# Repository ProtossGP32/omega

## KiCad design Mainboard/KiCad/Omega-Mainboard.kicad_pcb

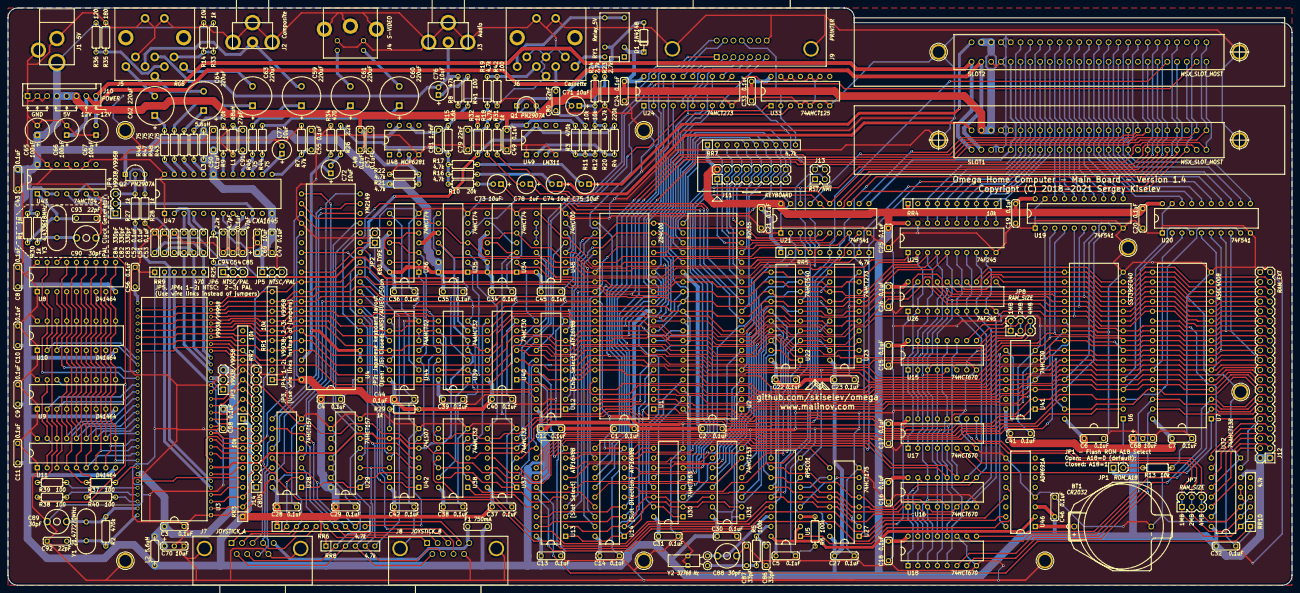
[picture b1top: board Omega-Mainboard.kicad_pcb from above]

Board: 2 copper layers, 333.4 x 149.9 mm, 248 parts (0 on the bottom side), 357 nets.

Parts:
BT1: CR2032; Battery_Holder_CR2032_Universal
C1, C2, C3, C4, C5, C6, C7, C8, C9, C10, C11, C12, C13, C14, C15, C16, C17, C18, C19, C20, C21, C22, C23, C24, C25, C26, C27, C28, C29, C30, C31, C32, C33, C34, C35, C36, C37, C38, C39, C40, C41, C42, C43, C44, C45, C46, C47, C48, C49, C50, C51, C52, C53, C54, C55, C56, C57, C58: 0.1uF; Cap_Cer_508
C59, C60, C61, C62, C63, C64: 220uF; Cap_Elec_Radial_10mm
C65, C66, C67: 100uF; Cap_Elec_Radial_6.3mm
C68, C69, C70: 10uF; Cap_Pol_508_3
C71, C72, C73, C74, C75, C76, C77: 10uF; Cap_Elec_Radial_5mm
C78: 1uF; Cap_Elec_Radial_5mm
C79, C80: 22nF; Cap_Cer_508
C81: 1.5nF; Cap_Cer_508
C82, C83, C84: 330pF; Cap_Cer_508
C85: 47pF; Cap_Cer_508
C86, C87: 33pF; Cap_Cer_508
C88, C89, C90: 30pF; C_Trim_Murata
C91: 27pF; Cap_Cer_508
C92, C93: 22pF; Cap_Cer_508
C94: 4.7pF; Cap_Cer_508
D1: 1N4148; Diode_762
F1: 750mA; Cap_Cer_508
HOLE1, HOLE2, HOLE3, HOLE4, HOLE5, HOLE6, HOLE7, HOLE8, HOLE9, HOLE10, HOLE11: HOLE; Hole_3mm
J1: 5V; Conn_Power_Jack_Circular_Pads
J2: Composite; Conn_RCA_Composite
J3: Audio; Conn_RCA_Audio
J4: S-VIDEO; Conn_Mini_DIN_4pin
J5: RGB; Conn_DIN_8pin
J6: Cassette; Conn_DIN_8pin
J7: JOYSTICK_A; Conn_Dsub_DE9M
J8: JOYSTICK_B; Conn_Dsub_DE9M
J9: PRINTER; Conn_Micro_Ribbon_14F
J10: POWER; Conn_Friction_Lock_8P_2.54mm
J11: KEYBOARD; Conn_Pin_Header_8x2_2.54mm
J12: RAM_EXT; Conn_Pin_Header_20x2_2.54mm
J13: ~RST~/~NMI; Conn_Pin_Header_2x2_2.54mm
J14: CBUS; Conn_Pin_Header_13x1_2.54mm
JP1: ROM_A18; Conn_Pin_Header_2x1_2.54mm
JP2: KBD_TYPE; Conn_Pin_Header_2x1_2.54mm
JP3, JP4: V9938/V9958; Conn_Pin_Header_3x1_2.54mm
JP5, JP6: NTSC/PAL; Conn_Pin_Header_3x1_2.54mm
JP7, JP8: RAM_SIZE; Conn_Pin_Header_2x3_2.54mm
L1: 68uH; Res_762
L2, L3: 5.6uH; Res_762
Q1, Q2: PN2907A; Transistor_TO92_EBC_254
R1: 1M; Res_762
R2, R3: 470k; Res_762
R4: 220k; Res_762
R5, R6: 100k; Res_762
R7, R8: 47k; Res_762
R9, R10: 20k; Res_762
R11, R12, R13, R14: 10k; Res_762
R15: 5.6k; Res_762
R16, R17, R18, R19, R20, R21, R22: 4.7k; Res_762
R23, R24: 2.7k; Res_762
R25, R26: 2.2k; Res_762
R27, R28, R29, R30, R31, R32, R33: 1k; Res_762
R34: 470; Res_762
R35: 180; Res_762
R36: 120; Res_762
R37, R38, R39, R40, R41, R42: 100; Res_762
R43, R44, R45, R46, R47, R48: 75; Res_762
RR1, RR2, RR3, RR4: 10k; Conn_SIL10
RR5, RR6, RR7: 4.7k; Conn_SIL10
RR8, RR10: 4.7k; Conn_SIL6
RR9: 470; Conn_SIL6
RY1: Relay_5V; Relay_SPDT
SLOT1, SLOT2: MSX_SLOT_HOST; Conn_Edge_50P
U1: Z84C00; IC_DIP40_600
U2: 82C55; IC_DIP40_600
U3: V9938/V9958; IC_SDIP64_600
U4: YM2149; IC_DIP40_600
U5: RP5C01; IC_DIP18_300
U6: SST39SF040; IC_DIP32_600
U7: AS6C4008; IC_DIP32_600
U8, U9, U10, U11: D41464; IC_DIP18_300
U12, U13, U14: ATF16V8B; IC_DIP20_300
U15, U16, U17, U18: 74HCT670; IC_DIP16_300
U19, U20, U21: 74F541; IC_DIP20_300
U22: 74HCT540; IC_DIP20_300
U23, U24: 74HCT273; IC_DIP20_300
U25, U26: 74F245; IC_DIP20_300
U27: 74HCT175; IC_DIP16_300
U28, U29: 74HCT157; IC_DIP16_300
U30, U31: 74HCT153; IC_DIP16_300
U32: 74AHCT138; IC_DIP16_300
U33: 74AHCT125; IC_DIP14_300
U34, U35, U36: 74HCT74; IC_DIP14_300
U37, U38, U39: 74AHCT32; IC_DIP14_300
U40, U41: 74HCT30; IC_DIP14_300
U42: 74LS07; IC_DIP14_300
U43: 74HCT04; IC_DIP14_300
U44: 74AHCT02; IC_DIP14_300
U45: 74HCT00; IC_DIP14_300
U46: ADM691A; IC_DIP16_300
U47: CXA1645; IC_DIP24_400
U48: MCP6281; IC_DIP8_300
U49: LM311; IC_DIP8_300
Y1: 21.477270MHz; Crystal_HC-49U_Vert
Y2: 32768 Hz; Crystal_32K_Horiz
Y3: 4.433618MHz; Crystal_HC-49U_Vert

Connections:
/A0: J12.31, U1.30, U2.9, U3.29, U6.12, U7.12, U12.9, U15.5, U15.14, U16.5, U16.14, U17.14, U18.14, U19.7, U40.12, U44.9
/A1: J12.29, U1.31, U2.8, U3.28, U6.11, U7.11, U15.4, U15.13, U16.4, U16.13, U17.13, U18.13, U19.6, U40.11, U44.11
/A2: J12.27, U1.32, U6.10, U7.10, U12.8, U19.5, U40.6
/A3: J12.25, U1.33, U6.9, U7.9, U12.7, U19.4, U40.5
/A4: J12.23, U1.34, U6.8, U7.8, U12.6, U19.3, U40.4
/A5: J12.21, U1.35, U6.7, U7.7, U12.5, U19.2, U40.3
/A6: J12.19, U1.36, U6.6, U7.6, U12.4, U20.5, U40.2
/A7: J12.17, U1.37, U6.5, U7.5, U12.3, U20.4, U40.1
/A8: J12.20, U1.38, U6.27, U7.27, U20.3, U41.11
/A9: J12.22, U1.39, U6.26, U7.26, U20.8, U41.5
/A10: J12.28, U1.40, U6.23, U7.23, U20.7, U41.4
/A11: J12.24, U1.1, U6.25, U7.25, U20.6, U41.6
/A12: J12.15, U1.2, U6.4, U7.4, U20.2, U41.3
/A13: J12.18, U1.3, U6.28, U7.28, U19.9, U41.12
/A14: U1.4, U6.29, U13.2, U14.2, U17.5, U18.5, U19.8, U30.14, U31.14, U41.2
/A15: U1.5, U6.3, U13.1, U14.1, U17.4, U18.4, U20.9, U30.2, U31.2, U41.1
/AUDIO: C76.2, J3.1, J5.2, R8.1
/CAS_IN: R4.2, R32.1, U4.14, U49.7
/CAS_MOT: R31.1, U2.13
/CAS_OUT: C78.1, U2.12
/CLK: U3.8, U21.9, U35.11, U39.4, U39.5, U42.5, U42.9
/D0: RR1.3, U1.14, U2.34, U3.40, U4.37, U5.11, U16.3, U16.6, U18.3, U22.18, U23.3, U24.17, U25.9, U26.9, U27.5, U35.2
/D1: RR1.4, U1.15, U2.33, U3.39, U4.36, U5.12, U16.2, U16.7, U18.2, U22.17, U23.18, U24.14, U25.8, U26.8, U27.4, U33.3
/D2: RR1.5, U1.12, U2.32, U3.38, U4.35, U5.13, U16.1, U16.9, U18.1, U22.16, U23.17, U24.4, U25.7, U26.7, U27.12
/D3: RR1.6, U1.8, U2.31, U3.37, U4.34, U5.14, U16.10, U16.15, U18.15, U22.15, U23.4, U24.7, U25.6, U26.6, U27.13
/D4: RR1.7, U1.7, U2.30, U3.36, U4.33, U15.3, U15.6, U17.3, U22.14, U23.7, U24.13, U25.5, U26.5
/D5: JP8.5, JP8.6, RR1.8, U1.9, U2.29, U3.35, U4.32, U15.2, U15.7, U17.2, U22.13, U23.14, U24.8, U25.4, U26.4
/D6: JP8.1, JP8.2, RR1.9, U1.10, U2.28, U3.34, U4.31, U15.10, U15.15, U17.15, U22.12, U23.13, U24.18, U25.3, U26.3
/D7: JP8.3, JP8.4, RR1.10, U1.13, U2.27, U3.32, U4.30, U15.1, U15.9, U17.1, U22.11, U23.8, U24.3, U25.2, U26.2
/KANA_LED: J11.14, U4.6
/KEY_CLICK: C73.1, U2.10
/Memory/MD0: J12.33, U6.13, U7.13, U26.11
/Memory/MD1: J12.35, U6.14, U7.14, U26.12
/Memory/MD2: J12.37, U6.15, U7.15, U26.13
/Memory/MD3: J12.38, U6.17, U7.17, U26.14
/Memory/MD4: J12.36, U6.18, U7.18, U26.15
/Memory/MD5: J12.34, U6.19, U7.19, U26.16
/Memory/MD6: J12.32, U6.20, U7.20, U26.17
/Memory/MD7: J12.30, U6.21, U7.21, U26.18
/Memory/RAM_A14: J12.13, U7.3, U18.6
/Memory/RAM_A15: J12.12, U7.31, U18.7
/Memory/RAM_A16: J12.11, U7.2, U18.9
/Memory/RAM_A17: J12.14, U7.30, U18.10
/Memory/RAM_A18: J12.9, U7.1, U17.6
/Memory/RAM_A19: JP7.1, JP7.2, RR10.2, U17.7, U32.1
/Memory/RAM_A20: JP7.3, JP7.4, RR10.3, U17.10, U32.2
/Memory/RAM_A21: JP7.5, JP7.6, RR10.4, U17.9, U32.3
/Memory/ROM_A18: JP1.2, R13.1, U6.1
/Memory/~PAGE_RD: U15.11, U16.11, U37.3
/Memory/~PAGE_WR: U15.12, U16.12, U17.12, U18.12, U37.11
/Memory/~RAM0_CS: U7.22, U32.15
/Memory/~RAM1_CS: J12.4, U32.14
/Memory/~RAM2_CS: J12.3, U32.13
/Memory/~RAM3_CS: J12.6, U32.12
/Memory/~RAM4_CS: J12.5, U32.11
/Memory/~RAM5_CS: J12.8, U32.10
/Memory/~RAM6_CS: J12.7, U32.9
/Memory/~RAM7_CS: J12.10, U32.7
/PPI/CAPS_LED: J11.12, U2.11
/PPI/COLUMN0: J11.1, RR7.2, U2.18
/PPI/COLUMN1: J11.3, RR7.3, U2.19
/PPI/COLUMN2: J11.5, RR7.4, U2.20
/PPI/COLUMN3: J11.7, RR7.5, U2.21
/PPI/COLUMN4: J11.9, RR7.6, U2.22
/PPI/COLUMN5: J11.11, RR7.7, U2.23
/PPI/COLUMN6: J11.13, RR7.8, U2.24
/PPI/COLUMN7: J11.15, RR7.9, U2.25
/PPI/ROW_A: J11.4, U2.14
/PPI/ROW_B: J11.6, U2.15
/PPI/ROW_C: J11.8, U2.16
/PPI/ROW_D: J11.10, U2.17
/PPI/SB_SLT_A: U13.6, U31.7
/PPI/SB_SLT_B: U13.7, U31.9
/PPI/SLT_A: U13.8, U30.7
/PPI/SLT_B: U13.9, U30.9
/PPI/~FFFF: U13.5, U38.2, U38.6
/PPI/~SLTSL3: U13.17, U38.1
/PPI/~SUB_RD: U22.1, U22.19, U38.11
/PPI/~SUB_REG_CS: U38.3, U38.10, U38.12
/PPI/~SUB_WR: U23.11, U38.8
/PRT_BUSY: J9.11, RR7.10, U33.2
/PSG/JB0: U4.13, U42.1
/PSG/JB1: U4.12, U42.13
/PSG/JB2: U4.11, U42.11
/PSG/JB3: U4.10, U42.3
/PSG/JOY_BCK: U4.20, U28.7
/PSG/JOY_FWD: U4.21, U28.4
/PSG/JOY_LFT: U4.19, U28.9
/PSG/JOY_OUT_A: J7.8, U4.9
/PSG/JOY_OUT_B: J8.8, U4.8
/PSG/JOY_RGT: U4.18, U28.12
/PSG/JOY_SEL: U4.7, U28.1, U29.1
/PSG/JOY_TRG1: U4.17, U29.4
/PSG/JOY_TRG2: U4.16, U29.7
/PSG/KBD_TYPE: JP2.1, RR8.6, U4.15
/PSG/PSG_BC1: U4.29, U44.10
/PSG/PSG_BDIR: U4.27, U44.13
/PSG/~BCK_A: J7.2, RR6.3, U28.5
/PSG/~BCK_B: J8.2, RR6.7, U28.6
/PSG/~FWD_A: J7.1, RR6.2, U28.2
/PSG/~FWD_B: J8.1, RR6.6, U28.3
/PSG/~LFT_A: J7.3, RR6.4, U28.11
/PSG/~LFT_B: J8.3, RR6.8, U28.10
/PSG/~RGT_A: J7.4, RR6.5, U28.14
/PSG/~RGT_B: J8.4, RR6.9, U28.13
/PSG/~TRG1_A: J7.6, RR8.3, U29.2, U42.2
/PSG/~TRG1_B: J8.6, RR8.4, U29.3, U42.12
/PSG/~TRG2_A: J7.7, RR8.2, U29.5, U42.10
/PSG/~TRG2_B: J8.7, RR8.5, U29.6, U42.4
/PSG_SND: C72.1, R34.1, U4.3, U4.4, U4.38
/Processor/ALARM: RR1.2, U5.15
/Processor/PD0: J9.2, U24.16
/Processor/PD1: J9.3, U24.15
/Processor/PD2: J9.4, U24.5
/Processor/PD3: J9.5, U24.6
/Processor/PD4: J9.6, U24.12
/Processor/PD5: J9.7, U24.9
/Processor/PD6: J9.8, U24.19
/Processor/PD7: J9.9, U24.2
/Processor/RTC_VCC: C5.1, U5.2, U5.18, U46.2
/Processor/~BUSREQ: RR5.3, U1.25
/Processor/~INT: U1.16, U45.8
/Processor/~NMI: J13.3, RR5.4, U1.17
/Processor/~PRT_BSY_RD: U33.1, U37.6
/Processor/~PRT_CMD_CS: U12.13, U37.5, U37.10
/Processor/~PRT_DAT_WR: U12.12, U24.11
/Processor/~PRT_STB_WR: U35.3, U37.8
/Processor/~RTC_AD_WR: U12.17, U27.9
/Processor/~RTC_CS: U12.16, U46.13
/Processor/~RTC_CS_B: U5.1, U46.12
/Processor/~STROBE: J9.1, U35.5
/RESET: U2.35, U46.16
/ROM_A16: U6.2, U13.13
/ROM_A17: U6.30, U13.12
/SLT1_SND: C74.1, SLOT1.49
/SLT2_SND: C75.1, SLOT2.49
/Slots/BA0: SLOT1.28, SLOT2.28, U19.13
/Slots/BA1: SLOT1.27, SLOT2.27, U19.14
/Slots/BA2: SLOT1.30, SLOT2.30, U19.15
/Slots/BA3: SLOT1.29, SLOT2.29, U19.16
/Slots/BA4: SLOT1.32, SLOT2.32, U19.17
/Slots/BA5: SLOT1.31, SLOT2.31, U19.18
/Slots/BA6: SLOT1.22, SLOT2.22, U20.15
/Slots/BA7: SLOT1.21, SLOT2.21, U20.16
/Slots/BA8: SLOT1.24, SLOT2.24, U20.17
/Slots/BA9: SLOT1.17, SLOT2.17, U20.12
/Slots/BA10: SLOT1.20, SLOT2.20, U20.13
/Slots/BA11: SLOT1.19, SLOT2.19, U20.14
/Slots/BA12: SLOT1.23, SLOT2.23, U20.18
/Slots/BA13: SLOT1.26, SLOT2.26, U19.11
/Slots/BA14: SLOT1.25, SLOT2.25, U19.12
/Slots/BA15: SLOT1.18, SLOT2.18, U20.11
/Slots/BD0: RR4.10, SLOT1.34, SLOT2.34, U25.11
/Slots/BD1: RR4.9, SLOT1.33, SLOT2.33, U25.12
/Slots/BD2: RR4.8, SLOT1.36, SLOT2.36, U25.13
/Slots/BD3: RR4.7, SLOT1.35, SLOT2.35, U25.14
/Slots/BD4: RR4.6, SLOT1.38, SLOT2.38, U25.15
/Slots/BD5: RR4.5, SLOT1.37, SLOT2.37, U25.16
/Slots/BD6: RR4.4, SLOT1.40, SLOT2.40, U25.17
/Slots/BD7: RR4.3, SLOT1.39, SLOT2.39, U25.18
/Slots/B_CLK: SLOT1.42, SLOT2.42, U21.11
/Slots/SLT_DIR: U14.12, U25.1
/Slots/~B_IORQ: SLOT1.11, SLOT2.11, U14.8, U21.15
/Slots/~B_M1: SLOT1.9, SLOT2.9, U14.7, U21.16
/Slots/~B_MREQ: SLOT1.12, SLOT2.12, U21.14
/Slots/~B_RD: SLOT1.14, SLOT2.14, U14.9, U21.18
/Slots/~B_RESET: SLOT1.15, SLOT2.15, U21.12
/Slots/~B_RFSH: SLOT1.6, SLOT2.6, U21.13
/Slots/~B_WR: SLOT1.13, SLOT2.13, U21.17
/Slots/~CS1: SLOT1.1, SLOT2.1, U14.14
/Slots/~CS2: SLOT1.2, SLOT2.2, U14.15
/Slots/~CS12: SLOT1.3, SLOT2.3, U14.13
/VDP/AV: J5.3, R14.2, R33.1
/VDP/BLUE: C53.1, C84.1, RR9.6, U3.24
/VDP/BOUT: C64.2, J5.8
/VDP/CB0: J14.12, RR2.6, U3.19
/VDP/CB1: J14.11, RR2.5, U3.18
/VDP/CB2: J14.10, RR2.4, U3.17
/VDP/CB3: J14.9, RR2.3, U3.16
/VDP/CB4: J14.8, RR2.2, U3.15
/VDP/CB5: J14.7, RR3.10, U3.14
/VDP/CB6: J14.6, RR3.9, U3.13
/VDP/CB7: J14.5, RR3.8, U3.12
/VDP/CBDR: J14.4, U3.11
/VDP/CHROMA: C60.2, J4.4
/VDP/COMP: C59.2, J2.1, J5.4
/VDP/CSYNC: R27.2, U3.6
/VDP/GOUT: C63.2, J5.7
/VDP/GREEN: C52.1, C83.1, RR9.4, U3.22
/VDP/HSYNC: RR9.2, U3.5
/VDP/LUMA: C61.2, J4.3
/VDP/PAL_CLK: JP6.3, U43.4
/VDP/RED: C51.1, C82.1, RR9.5, U3.23
/VDP/ROUT: C62.2, J5.6
/VDP/SYNCIN: C85.1, JP4.2, U47.10
/VDP/VA0: U3.49, U8.14, U9.14, U10.14, U11.14
/VDP/VA1: U3.50, U8.13, U9.13, U10.13, U11.13
/VDP/VA2: U3.51, U8.12, U9.12, U10.12, U11.12
/VDP/VA3: U3.52, U8.11, U9.11, U10.11, U11.11
/VDP/VA4: U3.53, U8.8, U9.8, U10.8, U11.8
/VDP/VA5: U3.54, U8.7, U9.7, U10.7, U11.7
/VDP/VA6: U3.55, U8.6, U9.6, U10.6, U11.6
/VDP/VA7: U3.56, U8.10, U9.10, U10.10, U11.10
/VDP/VD0: U3.41, U8.2, U10.2
/VDP/VD1: U3.42, U8.3, U10.3
/VDP/VD2: U3.43, U8.15, U10.15
/VDP/VD3: U3.44, U8.17, U10.17
/VDP/VD4: U3.45, U9.2, U11.2
/VDP/VD5: U3.46, U9.3, U11.3
/VDP/VD6: U3.47, U9.15, U11.15
/VDP/VD7: U3.48, U9.17, U11.17
/VDP/VIDEO: JP3.2, U3.21
/VDP/YS: J5.5, R35.2, R36.1
/VDP/~CAS0: R38.1, U8.16, U9.16
/VDP/~CAS1: R39.1, U10.16, U11.16
/VDP/~DHCLK: J14.2, RR3.2, U3.2
/VDP/~DLCLK: J14.3, RR3.3, U3.3
/VDP/~RAS: R40.1, U8.5, U9.5, U10.5, U11.5
/VDP/~VDP_RD: U3.31, U39.3
/VDP/~VDP_WR: U3.30, U39.11
/VDP/~VWR: R37.1, U8.4, U9.4, U10.4, U11.4
/~BUSDIR1: RR5.7, SLOT1.10, U14.5
/~BUSDIR2: RR5.6, SLOT2.10, U14.6
/~IORQ: U1.20, U12.2, U21.5
/~KBD_WAIT: RR5.2, U14.16
/~M1: U1.27, U12.11, U21.4, U34.2
/~M1_WAIT: U14.18, U34.5, U34.12
/~MEM_RD: U13.16, U26.1
/~MREQ: U1.19, U13.3, U21.6
/~PAGE_CS: U12.15, U37.2, U37.12
/~PPI_CS: U2.6, U12.14, U45.4
/~PSG_CS: U12.19, U39.9, U44.5, U44.6
/~RAM_SL: U13.15, U32.4, U32.5
/~RD: J12.26, U1.21, U2.5, U5.8, U6.24, U7.24, U13.11, U21.2, U37.1, U37.4, U38.13, U39.1
/~RESET: J13.1, U1.26, U3.9, U4.23, U21.8, U23.1, U24.1, U27.1, U35.4, U45.2, U46.15
/~RFSH: U1.28, U13.4, U21.7
/~ROM_CS: U6.22, U13.14
/~SLTSL1: SLOT1.4, U13.19, U14.3
/~SLTSL2: SLOT2.4, U13.18, U14.4
/~SLT_INT: RR5.9, SLOT1.8, SLOT2.8, U45.13
/~SLT_WAIT: RR5.10, SLOT1.7, SLOT2.7, U14.11
/~VDP_CS: U12.18, U39.2, U39.13
/~VDP_INT: RR2.7, U3.25, U45.12
/~VDP_WAIT: RR2.8, U3.26, U14.17
/~WAIT: U1.24, U14.19
/~WR: J12.16, U1.22, U2.36, U5.10, U6.31, U7.29, U12.1, U21.3, U37.9, U37.13, U38.9, U39.12
GND: BT1.2, C1.2, C2.2, C3.2, C4.2, C5.2, C6.2, C7.2, C8.2, C9.2, C10.2, C11.2, C12.2, C13.2, C14.2, C15.2, C16.2, C17.2, C18.2, C19.2, C20.2, C21.2, C22.2, C23.2, C24.2, C25.2, C26.2, C27.2, C28.2, C29.2, C30.2, C31.2, C32.2, C33.2, C34.2, C35.2, C36.2, C37.2, C38.2, C39.2, C40.2, C41.2, C42.2, C43.2, C44.2, C45.2, C46.2, C47.2, C48.2, C49.2, C50.2, C54.2, C55.2, C56.1, C57.2, C58.2, C65.2, C66.2, C67.1, C68.2, C69.2, C70.2, C71.2, C77.2, C79.2, C82.2, C83.2, C84.2, C85.2, C86.1, C87.1, C88.1, C89.1, C90.1, C92.1, C93.1, C94.2, HOLE1.1, HOLE2.1, HOLE3.1, HOLE4.1, HOLE5.1, HOLE6.1, HOLE7.1, HOLE8.1, HOLE9.1, HOLE10.1, HOLE11.1, J1.2, J1.3, J2.2, J3.2, J4.1, J4.2, J4.~, J5.1, J6.1, J6.2, J6.3, J6.8, J7.9, J7.GND, J8.9, J8.GND, J9.14, J9.GND, J10.1, J10.2, J10.3, J11.16, J12.39, J12.40, J13.2, J13.4, J14.13, JP2.2, JP5.3, L1.2, Q1.3, R6.2, R7.2, R8.2, R9.2, R13.2, R14.1, R22.1, R23.2, R28.1, R34.2, R35.1, R42.2, RR9.1, RR10.1, SLOT1.41, SLOT1.43, SLOT1.44, SLOT1.46, SLOT2.41, SLOT2.43, SLOT2.44, SLOT2.46, U1.29, U2.7, U3.1, U3.20, U4.1, U4.24, U5.9, U6.16, U7.16, U8.1, U8.18, U9.1, U9.18, U10.1, U10.18, U11.1, U11.18, U12.10, U13.10, U14.10, U15.8, U16.8, U17.8, U17.11, U18.8, U18.11, U19.1, U19.10, U19.19, U20.1, U20.10, U20.19, U21.1, U21.10, U21.19, U22.10, U23.10, U24.10, U25.10, U25.19, U26.10, U26.19, U27.8, U28.8, U28.15, U29.8, U29.10, U29.11, U29.13, U29.14, U29.15, U30.8, U31.1, U31.8, U31.15, U32.8, U33.4, U33.5, U33.7, U33.9, U33.10, U33.12, U33.13, U34.7, U35.7, U36.7, U37.7, U38.7, U39.7, U40.7, U41.7, U42.7, U43.7, U43.9, U43.11, U43.13, U44.7, U45.7, U46.4, U46.9, U47.1, U47.24, U48.4, U49.1, U49.4, Y2.~
unnamed: BT1.1, U46.1
unnamed: C51.2, U47.2
unnamed: C52.2, U47.3
unnamed: C53.2, U47.4
unnamed: C54.1, U47.9
unnamed: C55.1, R7.1, U47.13
unnamed: C56.2, U3.33
unnamed: C57.1, R21.1, R22.2, U48.3
unnamed: C59.1, R43.1
unnamed: C60.1, R44.1
unnamed: C61.1, R45.1
unnamed: C62.1, R46.1
unnamed: C63.1, R47.1
unnamed: C64.1, R48.1
unnamed: C71.1, R12.2, R20.1, R23.1, R24.1
unnamed: C72.2, R26.2
unnamed: C73.2, R10.2
unnamed: C74.2, R16.2
unnamed: C75.2, R17.2
unnamed: C76.1, R41.2
unnamed: C77.1, U47.14
unnamed: C78.2, R18.1
unnamed: C79.1, R18.2, R19.1
unnamed: C80.1, J6.5
unnamed: C80.2, R11.2
unnamed: C81.1, R10.1, R15.1, R16.1, R17.1, R26.1, U48.2
unnamed: C81.2, R15.2, R41.1, U48.6
unnamed: C86.2, R5.1, U5.17
unnamed: C87.2, R5.2, Y2.2
unnamed: C88.2, U5.16, Y2.1
unnamed: C89.2, R2.2, U3.63, Y1.2
unnamed: C90.2, R30.1, Y3.2
unnamed: C91.1, U47.17
unnamed: C91.2, L1.1
unnamed: C92.2, R2.1, U3.64, Y1.1
unnamed: C93.2, R1.2, U43.1, Y3.1
unnamed: C94.1, R25.1, U47.6
unnamed: D1.2, Q1.1, RY1.9
unnamed: F1.1, J7.5, J8.5
unnamed: J6.4, R19.2, R42.1
unnamed: J6.6, RY1.5, RY1.6
unnamed: J6.7, RY1.10
unnamed: JP3.1, RR9.3
unnamed: JP4.1, U43.6
unnamed: JP4.3, Q2.2, R27.1
unnamed: JP5.2, U47.7
unnamed: JP6.1, U39.6
unnamed: JP6.2, R25.2
unnamed: Q1.2, R31.2
unnamed: Q2.3, R28.2, U43.5
unnamed: R1.1, R30.2, U43.2, U43.3
unnamed: R6.1, U5.3
unnamed: R9.1, U47.18
unnamed: R3.2, R11.1, R12.1, U49.3
unnamed: R4.1, R20.2, U49.2
unnamed: R29.2, U1.6, U34.3, U34.11, U42.8
unnamed: R37.2, U3.57
unnamed: R38.2, U3.61
unnamed: R39.2, U3.60
unnamed: R40.2, U3.62
unnamed: R43.2, U47.20
unnamed: R44.2, U47.15
unnamed: R45.2, U47.16
unnamed: R46.2, U47.23
unnamed: R47.2, U47.22
unnamed: R48.2, U47.21
unnamed: RR2.9, U3.27
unnamed: RR3.4, U3.4
unnamed: RR3.5, U3.59
unnamed: RR3.6, U3.7
unnamed: RR3.7, U3.10
unnamed: RR6.10, U36.3, U36.11, U42.6, U44.3
unnamed: U2.1, U30.11
unnamed: U2.2, U30.5
unnamed: U2.3, U30.10
unnamed: U2.4, U30.6
unnamed: U2.37, U30.13
unnamed: U2.38, U30.3
unnamed: U2.39, U30.12
unnamed: U2.40, U30.4
unnamed: U22.2, U23.2, U31.6
unnamed: U22.3, U23.19, U31.10
unnamed: U22.4, U23.16, U31.5
unnamed: U22.5, U23.5, U31.11
unnamed: U22.6, U23.6, U31.4
unnamed: U22.7, U23.15, U31.12
unnamed: U22.8, U23.12, U31.3
unnamed: U22.9, U23.9, U31.13
unnamed: U5.5, U27.2
unnamed: U5.4, U27.7
unnamed: U5.6, U27.10
unnamed: U5.7, U27.15
unnamed: U30.1, U30.15, U45.3, U45.5
unnamed: U34.4, U34.9
unnamed: U4.22, U35.9
unnamed: U35.8, U35.12
unnamed: U36.1, U36.2, U36.13, U44.4
unnamed: U36.8, U44.2
unnamed: U36.5, U36.12
unnamed: U38.4, U41.8
unnamed: U38.5, U40.8
unnamed: U39.8, U44.8, U44.12
unnamed: U39.10, U44.1
unnamed: U45.1, U45.6
unnamed: U45.9, U45.10, U45.11
VCC: C1.1, C2.1, C4.1, C6.1, C7.1, C8.1, C9.1, C10.1, C11.1, C12.1, C13.1, C14.1, C15.1, C16.1, C17.1, C18.1, C19.1, C20.1, C21.1, C22.1, C23.1, C24.1, C25.1, C26.1, C27.1, C28.1, C29.1, C30.1, C31.1, C32.1, C33.1, C34.1, C35.1, C36.1, C37.1, C38.1, C39.1, C40.1, C41.1, C42.1, C43.1, C44.1, C45.1, C46.1, C48.1, C49.1, C65.1, C68.1, D1.1, F1.2, J1.1, J10.4, J10.5, J10.6, J11.2, J12.1, J12.2, J14.1, JP1.1, L2.1, L3.1, Q2.1, R3.1, R21.2, R24.2, R29.1, R32.2, R33.2, R36.2, RR1.1, RR2.1, RR3.1, RR4.1, RR5.1, RR6.1, RR7.1, RR8.1, RY1.2, SLOT1.45, SLOT1.47, SLOT2.45, SLOT2.47, U1.11, U2.26, U4.25, U4.28, U4.40, U6.32, U7.32, U8.9, U9.9, U10.9, U11.9, U12.20, U13.20, U14.20, U15.16, U16.16, U17.16, U18.16, U19.20, U20.20, U21.20, U22.20, U23.20, U24.20, U25.20, U26.20, U27.16, U28.16, U29.16, U30.16, U31.16, U32.6, U32.16, U33.14, U34.1, U34.10, U34.13, U34.14, U35.1, U35.10, U35.13, U35.14, U36.4, U36.10, U36.14, U37.14, U38.14, U39.14, U40.14, U41.14, U42.14, U43.14, U44.14, U45.14, U46.3, U48.7, U49.8
VCCRGB: C47.1, C50.1, C69.1, JP5.1, L3.2, U47.12, U47.19
VCCVDP: C3.1, C58.1, C70.1, JP3.3, L2.2, U3.58
VDD: C66.1, J10.7, SLOT1.48, SLOT2.48
VSS: C67.2, J10.8, SLOT1.50, SLOT2.50

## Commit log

2021-10-22 Updated footprints: • All used footprints now point to the kicad-packages3d path • Footprints are stored in its own omega library: omega_components.pretty • Additional 3D models downloaded from exter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
2021-10-24 FIX: Updated again Omega-Mainboard.kicad_pcb with correct omega-components.pretty library links
2021-10-24 NEW: Added wavymega folder: • New measurements.md file with some additional measurements of additional modules
2022-02-07 UPD: Migrated project to KiCAD 6

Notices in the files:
Mainboard/KiCad/Omega-Mainboard.kicad_pcb:
Copyright (C) 2018-2021 Sergey Kiselev
